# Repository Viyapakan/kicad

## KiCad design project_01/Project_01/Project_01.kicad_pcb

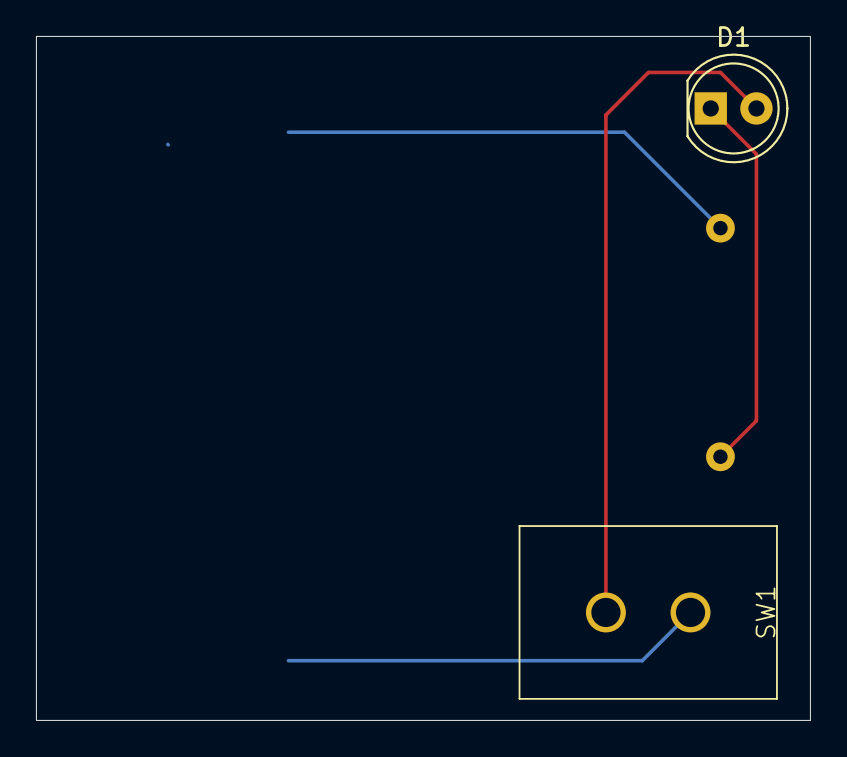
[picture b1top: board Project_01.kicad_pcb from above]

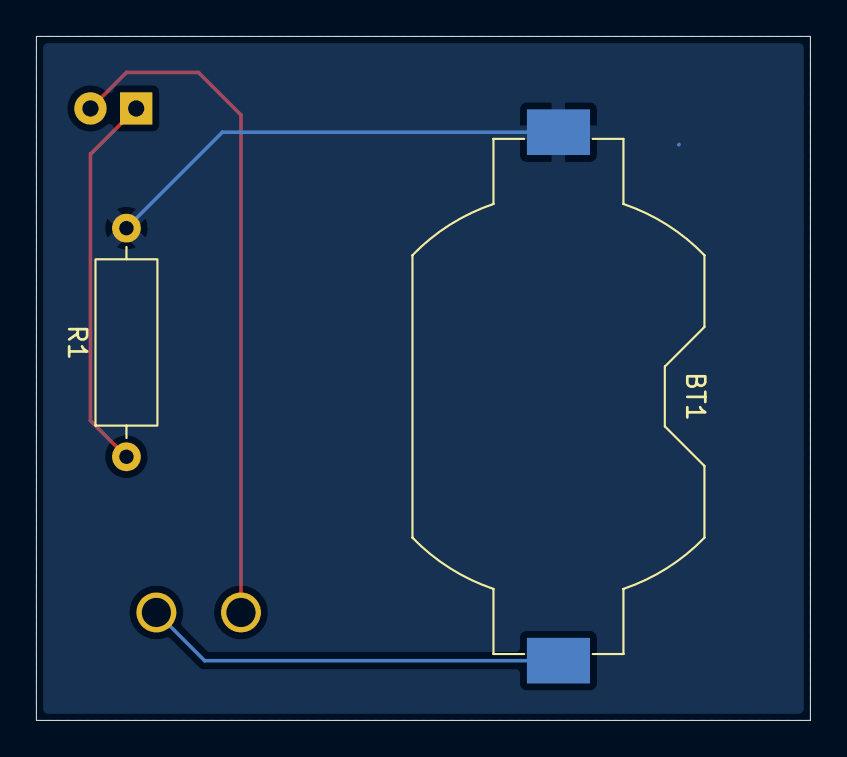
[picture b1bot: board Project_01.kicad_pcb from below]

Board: 2 copper layers, 43.0 x 38.0 mm, 4 parts (2 on the bottom side), 4 nets.

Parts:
BT1: 3V; BatteryHolder_Keystone_1058_1x2032
D1: RED; LED_D5.0mm
R1: 1K; R_Axial_DIN0309_L9.0mm_D3.2mm_P12.70mm_Horizontal
SW1: Switch_Toggle_SPST_NKK_M2011S3A1x03

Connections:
/LED: D1.1 (K), R1.1
GND: BT1.2 (-), R1.2
unnamed: BT1.1 (+), SW1.2 (A)
VCC: D1.2 (A), SW1.3 (B)
